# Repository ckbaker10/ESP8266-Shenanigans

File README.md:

To open PIO Projects change into the Folder e.g. VSCODE\Tuerklingel open a shell, run "code ."

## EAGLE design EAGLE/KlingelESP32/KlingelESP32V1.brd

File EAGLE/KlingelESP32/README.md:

https://www.mikrocontroller-elektronik.de/esp12e-tutorial-einstieg-mit-dem-esp8266-modul/

https://circuitjournal.com/esp8266-with-arduino-ide

PARTS:

1N5819 https://www.ebay.de/itm/334296315528

AO3401 https://www.ebay.de/itm/331839396676

AZ1117CR-3.3TRG1	https://www.tme.eu/de/en/details/az1117cr-3.3trg1/ldo-unregulated-voltage-regulators/diodes-incorporated/

EL814 https://www.tme.eu/de/en/details/el814/optocouplers-analog-output/everlight/

FUSE 0034.1512 https://www.tme.eu/de/en/details/0034.1512/fuses-5x20mm-fast/schurter/

Fuse Holder https://www.tme.eu/de/en/details/0751.0052/pcb-fuseholders/schurter/

AZ943-1CH-5DE https://www.tme.eu/de/en/details/az943-1ch-5de/miniature-electromagnetic-relays/zettler/

HW-613 https://www.aliexpress.com/item/32998165691.html?spm=a2g0o.productlist.0.0.21da5536koTBeC&algo_pvid=9d2d9b70-ff9a-4776-9e74-c352c65d18aa&algo_exp_id=9d2d9b70-ff9a-4776-9e74-c352c65d18aa-9&pdp_ext_f=%7B%22sku_id%22%3A%2266968306552%22%7D&pdp_pi=-1%3B3.23%3B-1%3B-1%40salePrice%3BUSD%3Bsearch-mainSearch

Search For "Mini DC-DC 12-24V to 5V 3A Step Down Module"

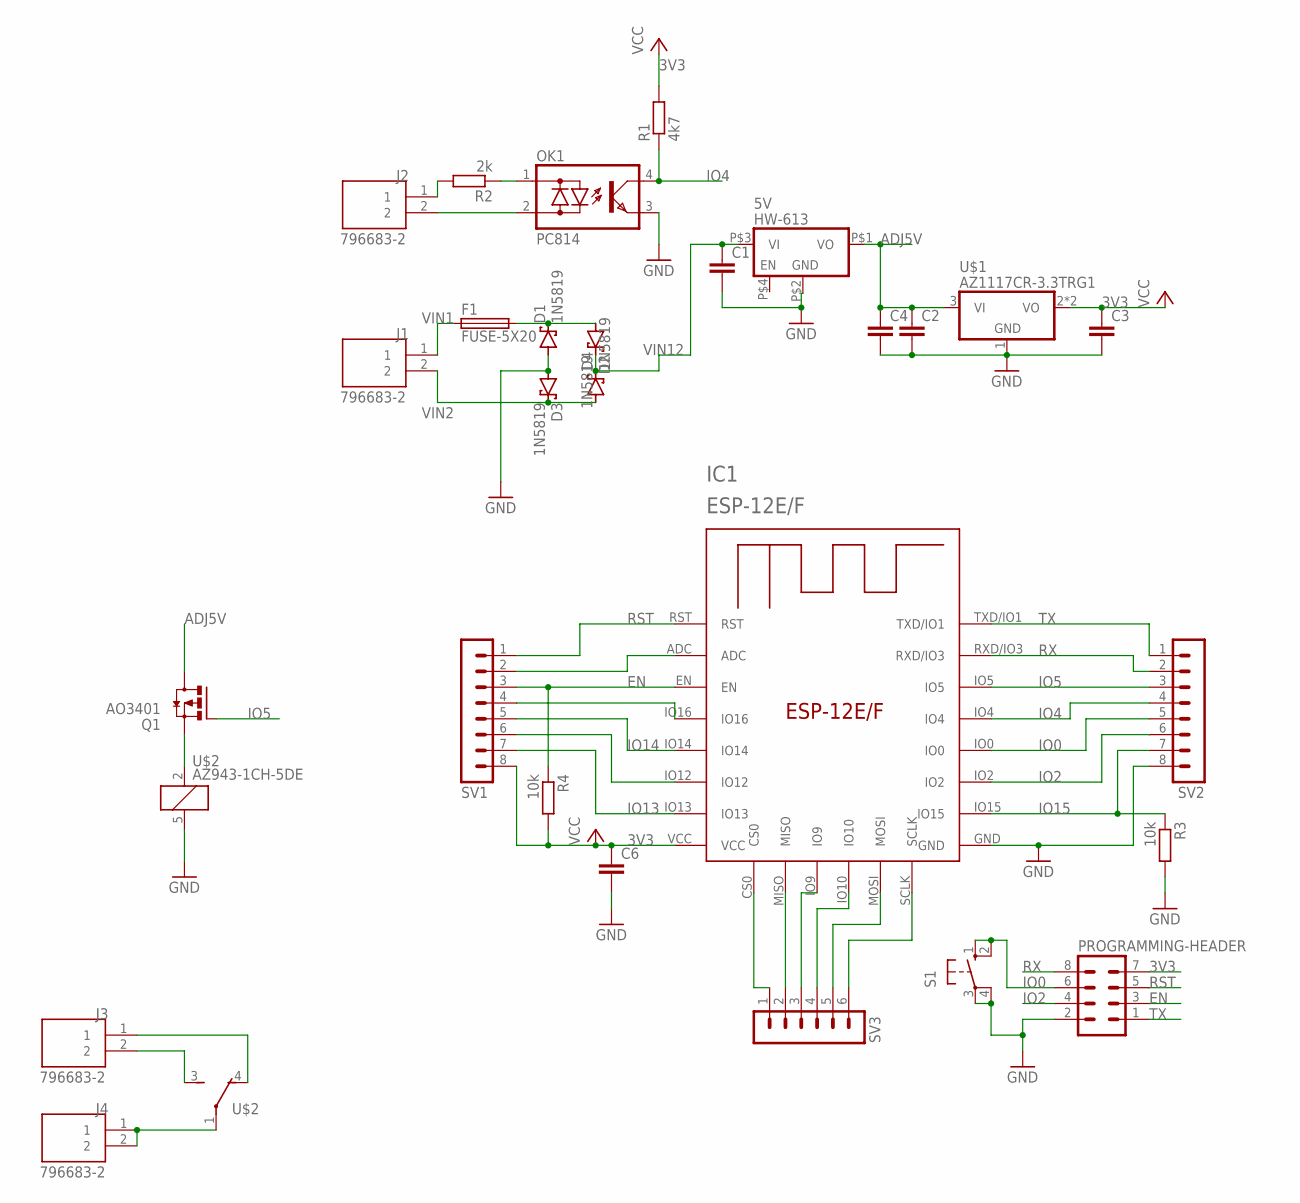
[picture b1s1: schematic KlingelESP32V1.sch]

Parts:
5V: HW-613
C1, C2, C3, C4, C6: C-EUC0805; C0805
D1, D2, D3, D4: 1N5819; DO41-7.6
F1: FUSE-5X20; 0751.0052
IC1: ESP-12E/F; ESP-12E
J1, J2, J3, J4: 796683-2; TE_796683-2
OK1: PC814; DIL04
PROGRAMMING-HEADER: MA04-2
Q1: AO3401; SUPER-SOT3
R1: 4k7; R0805
R2: 2k; R0805
R3, R4: 10k; R0805
S1: 10-XX; B3F-10XX
SV1, SV2: MA08-1
SV3: MA06-1
U$1: AZ1117CR-3.3TRG1; SOT89
U$2: AZ943-1CH-5DE

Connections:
3V3: C3.1, C6.1, IC1.VCC, PROGRAMMING-HEADER.7, R1.2, R4.2, SV1.8, U$1.2 (VO), U$1.2@1 (VO)
ADJ5V: 5V.P$1 (VO), C2.1, C4.1, Q1.3 (D), U$1.3 (VI)
EN: IC1.EN, PROGRAMMING-HEADER.3, R4.1, SV1.3
GND: 5V.P$2 (ADJ1), C1.2, C2.2, C3.2, C4.2, C6.2, D1.A, D3.A, IC1.GND, OK1.3 (E), PROGRAMMING-HEADER.2, R3.2, S1.3, S1.4 (P1), SV2.8, U$1.1 (GND), U$2.5 (2)
IO0: IC1.IO0, PROGRAMMING-HEADER.6, S1.1 (S), S1.2 (S1), SV2.5
IO2: IC1.IO2, PROGRAMMING-HEADER.4, SV2.6
IO4: IC1.IO4, OK1.4 (C), R1.1, SV2.4
IO5: IC1.IO5, Q1.1 (G), SV2.3
IO13: IC1.IO13, SV1.7
IO14: IC1.IO14, SV1.5
IO15: IC1.IO15, R3.1, SV2.7
unnamed: J2.1, R2.2
unnamed: IC1.CS0, SV3.1
unnamed: Q1.2 (S), U$2.2 (1)
unnamed: D1.C, D2.A, F1.P$3 (2), F1.P$4 (2)
unnamed: OK1.1 (AC1), R2.1
unnamed: J2.2, OK1.2 (AC2)
unnamed: IC1.MISO, SV3.2
unnamed: IC1.IO9, SV3.3
unnamed: IC1.IO10, SV3.4
unnamed: IC1.MOSI, SV3.5
unnamed: IC1.SCLK, SV3.6
unnamed: IC1.ADC, SV1.2
unnamed: IC1.IO16, SV1.4
unnamed: IC1.IO12, SV1.6
unnamed: J3.2, U$2.3 (S)
unnamed: J3.1, U$2.4 (O)
unnamed: J4.1, J4.2, U$2.1
RST: IC1.RST, PROGRAMMING-HEADER.5, SV1.1
RX: IC1.RXD/IO3, PROGRAMMING-HEADER.8, SV2.2
TX: IC1.TXD/IO1, PROGRAMMING-HEADER.1, SV2.1
VIN1: F1.P$1 (1), F1.P$2 (1), J1.1
VIN2: D3.C, D4.A, J1.2
VIN12: 5V.P$3 (VI), C1.1, D2.C, D4.C

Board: 2 copper layers, 29 parts (0 on the bottom side), 34 nets, no tracks yet.

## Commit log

2022-04-21 Another error in VCC usage...
2022-04-21 Parts list
